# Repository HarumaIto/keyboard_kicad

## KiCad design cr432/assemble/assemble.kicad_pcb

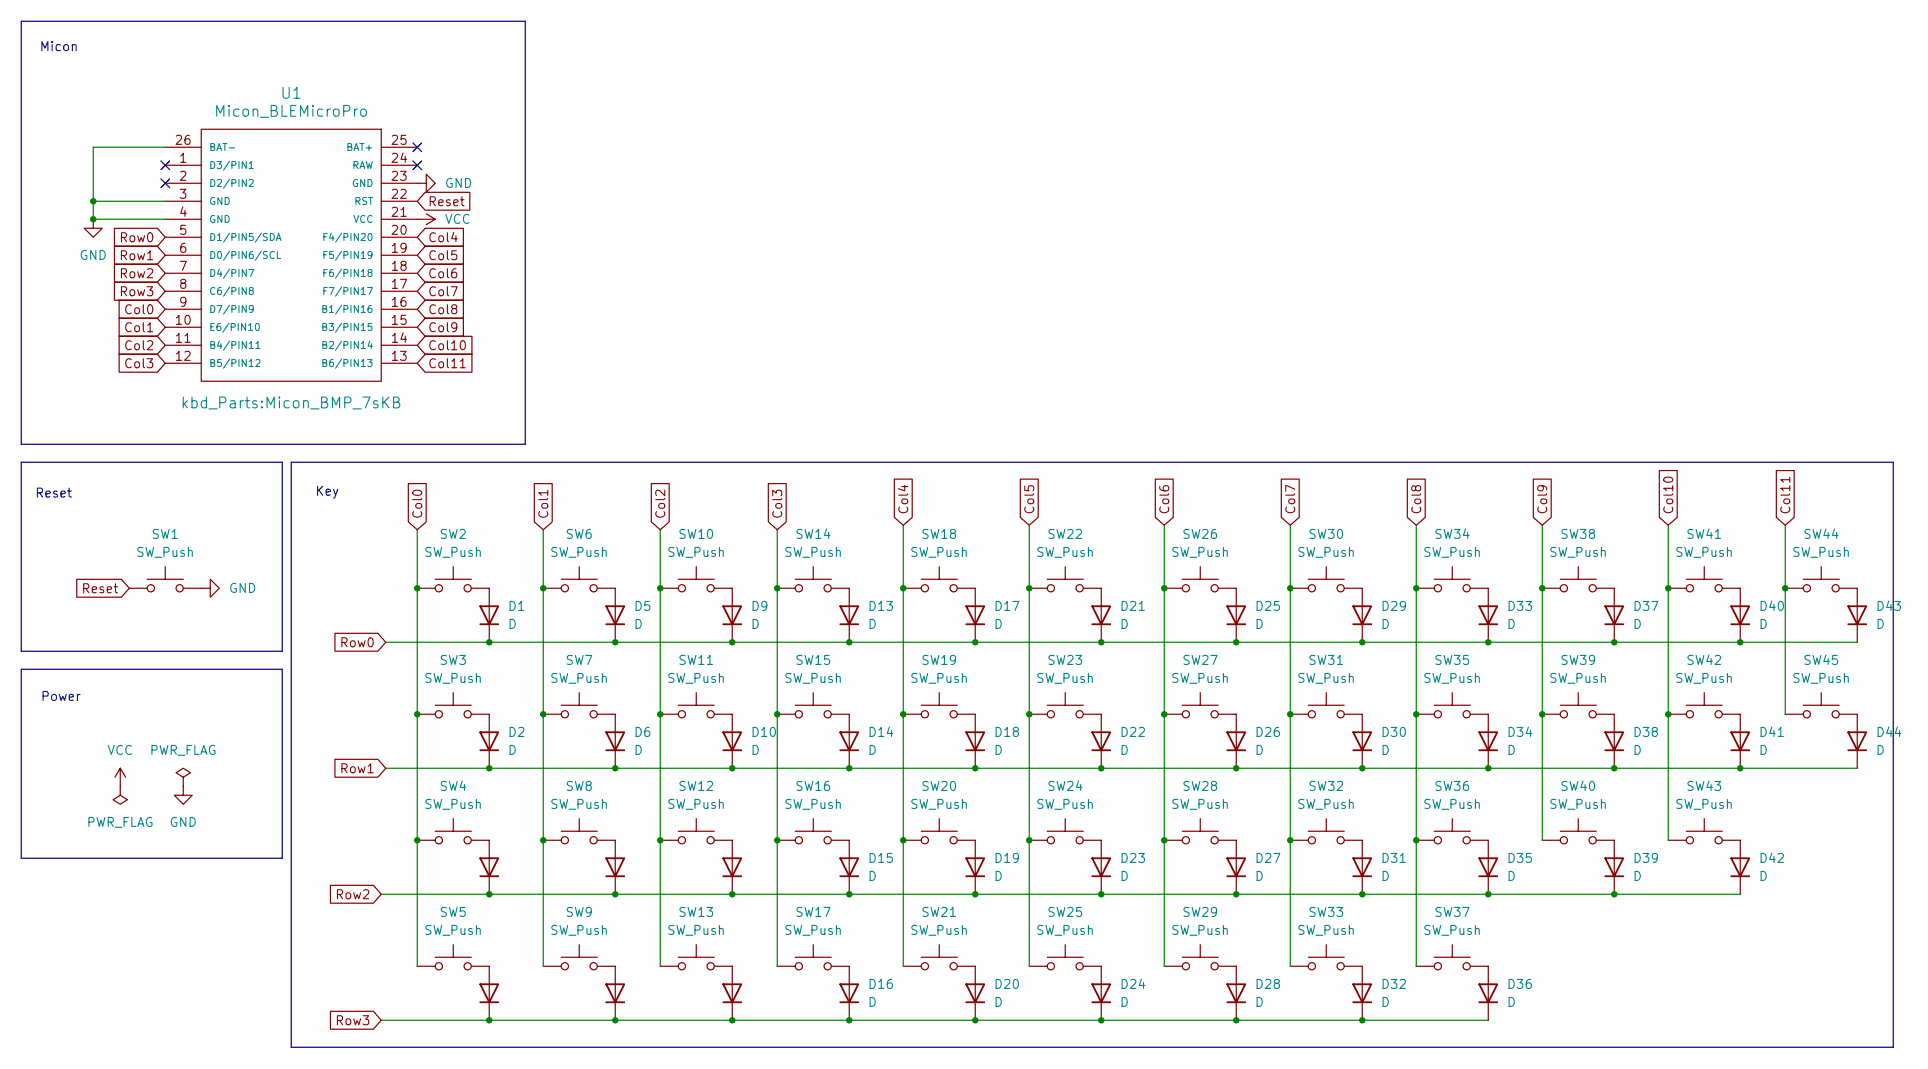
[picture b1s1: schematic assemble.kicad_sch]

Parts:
D1, D2, D3, D4, D5, D6, D7, D8, D9, D10, D11, D12, D13, D14, D15, D16, D17, D18, D19, D20, D21, D22, D23, D24, D25, D26, D27, D28, D29, D30, D31, D32, D33, D34, D35, D36, D37, D38, D39, D40, D41, D42, D43, D44: D; Diode_SMD
SW1: SW_Push; ResetSW
SW2, SW6, SW7, SW8, SW10, SW11, SW12, SW14, SW15, SW16, SW18, SW19, SW20, SW21, SW22, SW23, SW24, SW26, SW27, SW28, SW30, SW31, SW32, SW34, SW35, SW36, SW38, SW39, SW40, SW41, SW42: SW_Push; CherryMX_Hotswap_1u
SW3, SW5, SW9, SW13, SW29, SW33, SW37, SW45: SW_Push; CherryMX_Hotswap_1.25u
SW4, SW43: SW_Push; CherryMX_Hotswap_1.75u
SW17, SW25: SW_Push; CherryMX_Hotswap_2u
SW44: SW_Push; CherryMX_Hotswap_1.5u
U1: Micon_BLEMicroPro; Micon_BMP_7sKB

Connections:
Col0: SW2.1, SW3.1, SW4.1, SW5.1, U1.9 (D7/PIN9)
Col1: SW6.1, SW7.1, SW8.1, SW9.1, U1.10 (E6/PIN10)
Col2: SW10.1, SW11.1, SW12.1, SW13.1, U1.11 (B4/PIN11)
Col3: SW14.1, SW15.1, SW16.1, SW17.1, U1.12 (B5/PIN12)
Col4: SW18.1, SW19.1, SW20.1, SW21.1, U1.20 (F4/PIN20)
Col5: SW22.1, SW23.1, SW24.1, SW25.1, U1.19 (F5/PIN19)
Col6: SW26.1, SW27.1, SW28.1, SW29.1, U1.18 (F6/PIN18)
Col7: SW30.1, SW31.1, SW32.1, SW33.1, U1.17 (F7/PIN17)
Col8: SW34.1, SW35.1, SW36.1, SW37.1, U1.16 (B1/PIN16)
Col9: SW38.1, SW39.1, SW40.1, U1.15 (B3/PIN15)
Col10: SW41.1, SW42.1, SW43.1, U1.14 (B2/PIN14)
Col11: SW44.1, SW45.1, U1.13 (B6/PIN13)
GND: SW1.2, U1.3 (GND), U1.4 (GND), U1.23 (GND), U1.26 (BAT-)
unnamed: D1.2 (A), SW2.2
unnamed: D2.2 (A), SW3.2
unnamed: D3.2 (A), SW4.2
unnamed: D4.2 (A), SW5.2
unnamed: D5.2 (A), SW6.2
unnamed: D6.2 (A), SW7.2
unnamed: D7.2 (A), SW8.2
unnamed: D8.2 (A), SW9.2
unnamed: D9.2 (A), SW10.2
unnamed: D10.2 (A), SW11.2
unnamed: D11.2 (A), SW12.2
unnamed: D12.2 (A), SW13.2
unnamed: D13.2 (A), SW14.2
unnamed: D14.2 (A), SW15.2
unnamed: D15.2 (A), SW16.2
unnamed: D16.2 (A), SW17.2
unnamed: D17.2 (A), SW18.2
unnamed: D18.2 (A), SW19.2
unnamed: D19.2 (A), SW20.2
unnamed: D20.2 (A), SW21.2
unnamed: D21.2 (A), SW22.2
unnamed: D22.2 (A), SW23.2
unnamed: D23.2 (A), SW24.2
unnamed: D24.2 (A), SW25.2
unnamed: D25.2 (A), SW26.2
unnamed: D26.2 (A), SW27.2
unnamed: D27.2 (A), SW28.2
unnamed: D28.2 (A), SW29.2
unnamed: D29.2 (A), SW30.2
unnamed: D30.2 (A), SW31.2
unnamed: D31.2 (A), SW32.2
unnamed: D32.2 (A), SW33.2
unnamed: D33.2 (A), SW34.2
unnamed: D34.2 (A), SW35.2
unnamed: D35.2 (A), SW36.2
unnamed: D36.2 (A), SW37.2
unnamed: D37.2 (A), SW38.2
unnamed: D38.2 (A), SW39.2
unnamed: D39.2 (A), SW40.2
unnamed: D40.2 (A), SW41.2
unnamed: D41.2 (A), SW42.2
unnamed: D42.2 (A), SW43.2
unnamed: D43.2 (A), SW44.2
unnamed: D44.2 (A), SW45.2
Reset: SW1.1, U1.22 (RST)
Row0: D1.1 (K), D5.1 (K), D9.1 (K), D13.1 (K), D17.1 (K), D21.1 (K), D25.1 (K), D29.1 (K), D33.1 (K), D37.1 (K), D40.1 (K), D43.1 (K), U1.5 (D1/PIN5/SDA)
Row1: D2.1 (K), D6.1 (K), D10.1 (K), D14.1 (K), D18.1 (K), D22.1 (K), D26.1 (K), D30.1 (K), D34.1 (K), D38.1 (K), D41.1 (K), D44.1 (K), U1.6 (D0/PIN6/SCL)
Row2: D3.1 (K), D7.1 (K), D11.1 (K), D15.1 (K), D19.1 (K), D23.1 (K), D27.1 (K), D31.1 (K), D35.1 (K), D39.1 (K), D42.1 (K), U1.7 (D4/PIN7)
Row3: D4.1 (K), D8.1 (K), D12.1 (K), D16.1 (K), D20.1 (K), D24.1 (K), D28.1 (K), D32.1 (K), D36.1 (K), U1.8 (C6/PIN8)
VCC: U1.21 (VCC)

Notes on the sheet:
Power
Micon
Reset
Key

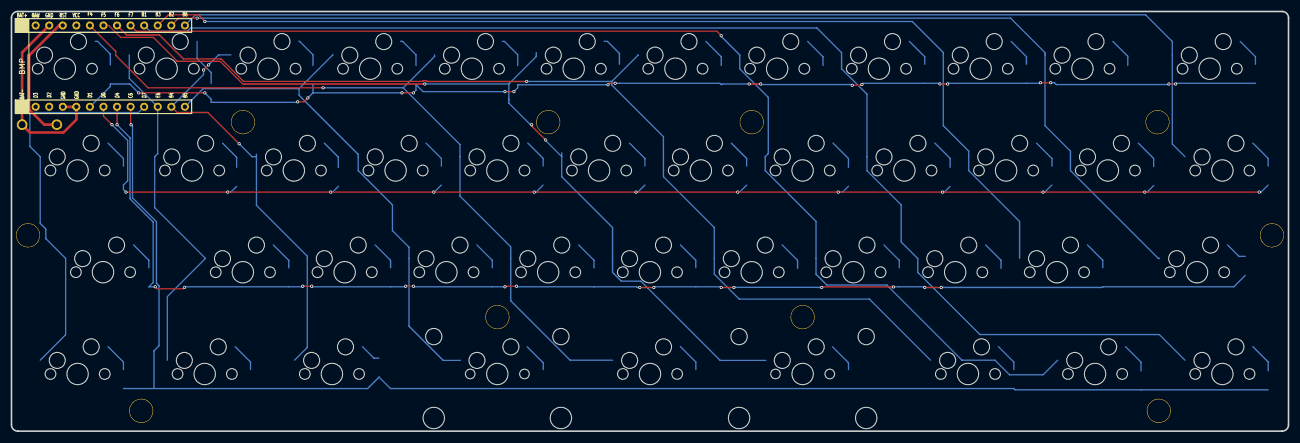
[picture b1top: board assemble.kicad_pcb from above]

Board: 2 copper layers, 239.1 x 78.6 mm, 100 parts (0 on the bottom side), 62 nets.

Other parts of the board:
Ref**: Val**; m2_Spacer_Hole
Ref**#2, Ref**#3, Ref**#4, Ref**#5, Ref**#6, Ref**#7, Ref**#8, Ref**#9, Ref**#10: Val**; m2_Spacer_Hole

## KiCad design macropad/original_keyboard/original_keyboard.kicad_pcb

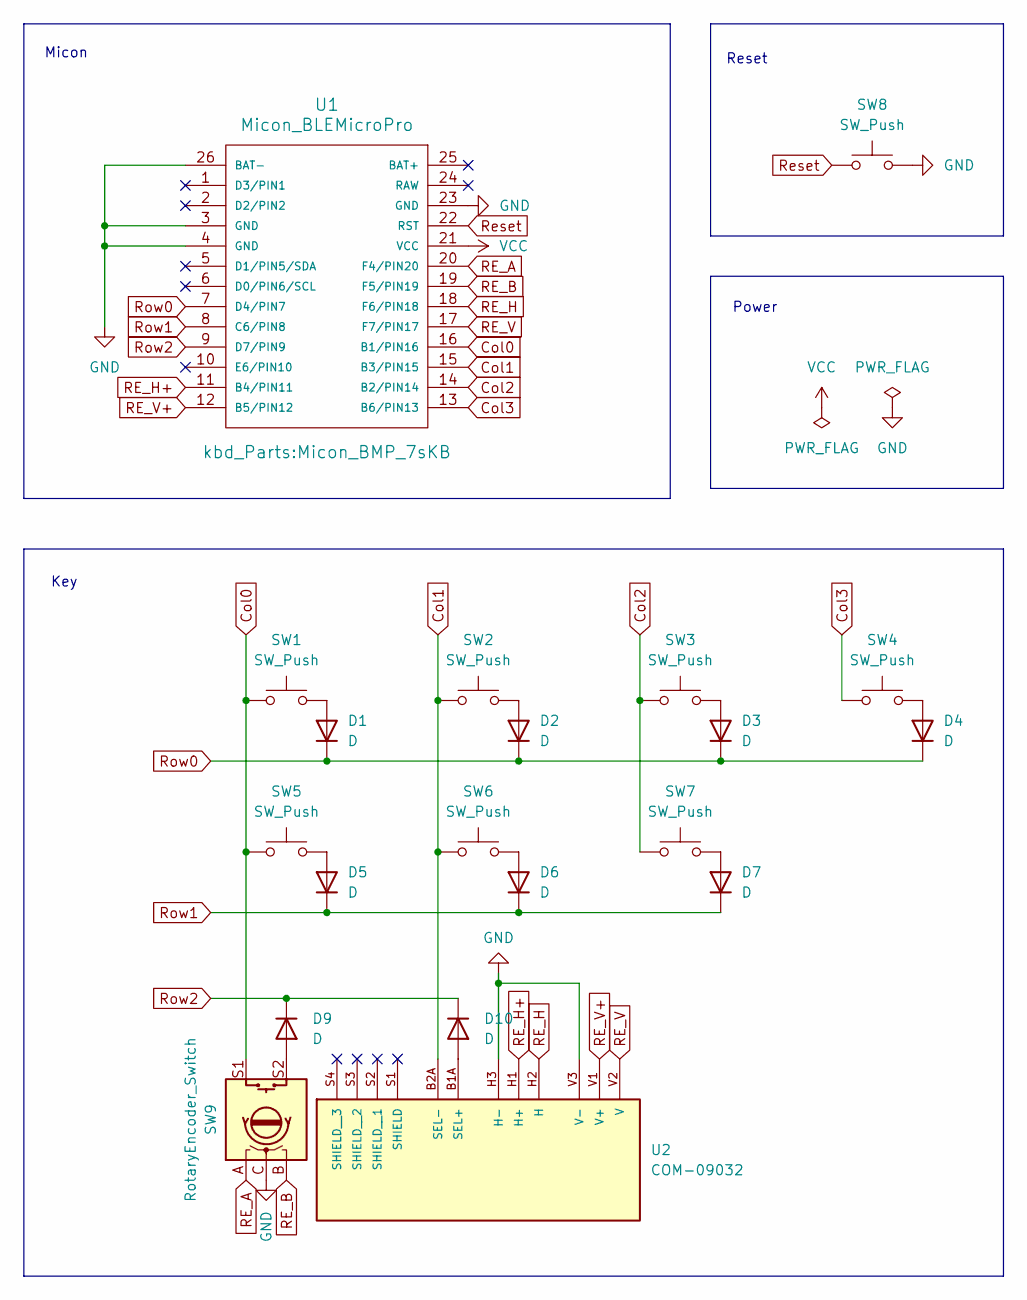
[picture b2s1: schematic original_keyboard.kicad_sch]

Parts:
D1, D2, D3, D4, D5, D6, D7, D9, D10: D; Diode_TH_SMD
SW1, SW2, SW3, SW4, SW5, SW6, SW7: SW_Push; Choc_v1_v2
SW8: SW_Push; ResetSW
SW9: RotaryEncoder_Switch; EVQWGD001
U1: Micon_BLEMicroPro; Micon_BMP_7sKB
U2: COM-09032; XDCR_COM-09032; PARTREV N/A

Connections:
Col0: SW1.1, SW5.1, SW9.S1, U1.16 (B1/PIN16)
Col1: SW2.1, SW6.1, U1.15 (B3/PIN15), U2.B2A (SEL-)
Col2: SW3.1, SW7.1, U1.14 (B2/PIN14)
Col3: SW4.1, U1.13 (B6/PIN13)
GND: SW8.2, SW9.C, U1.3 (GND), U1.4 (GND), U1.23 (GND), U1.26 (BAT-), U2.H3 (H-), U2.V3 (V-)
unnamed: D1.2 (A), SW1.2
unnamed: D2.2 (A), SW2.2
unnamed: D3.2 (A), SW3.2
unnamed: D4.2 (A), SW4.2
unnamed: D5.2 (A), SW5.2
unnamed: D6.2 (A), SW6.2
unnamed: D7.2 (A), SW7.2
unnamed: D9.2 (A), SW9.S2
unnamed: D10.2 (A), U2.B1A (SEL+)
RE_A: SW9.A, U1.20 (F4/PIN20)
RE_B: SW9.B, U1.19 (F5/PIN19)
RE_H: U1.18 (F6/PIN18), U2.H2 (H)
RE_H+: U1.11 (B4/PIN11), U2.H1 (H+)
RE_V: U1.17 (F7/PIN17), U2.V2 (V)
RE_V+: U1.12 (B5/PIN12), U2.V1 (V+)
Reset: SW8.1, U1.22 (RST)
Row0: D1.1 (K), D2.1 (K), D3.1 (K), D4.1 (K), U1.7 (D4/PIN7)
Row1: D5.1 (K), D6.1 (K), D7.1 (K), U1.8 (C6/PIN8)
Row2: D9.1 (K), D10.1 (K), U1.9 (D7/PIN9)
VCC: U1.21 (VCC)

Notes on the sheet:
Reset
Power
Micon
Key

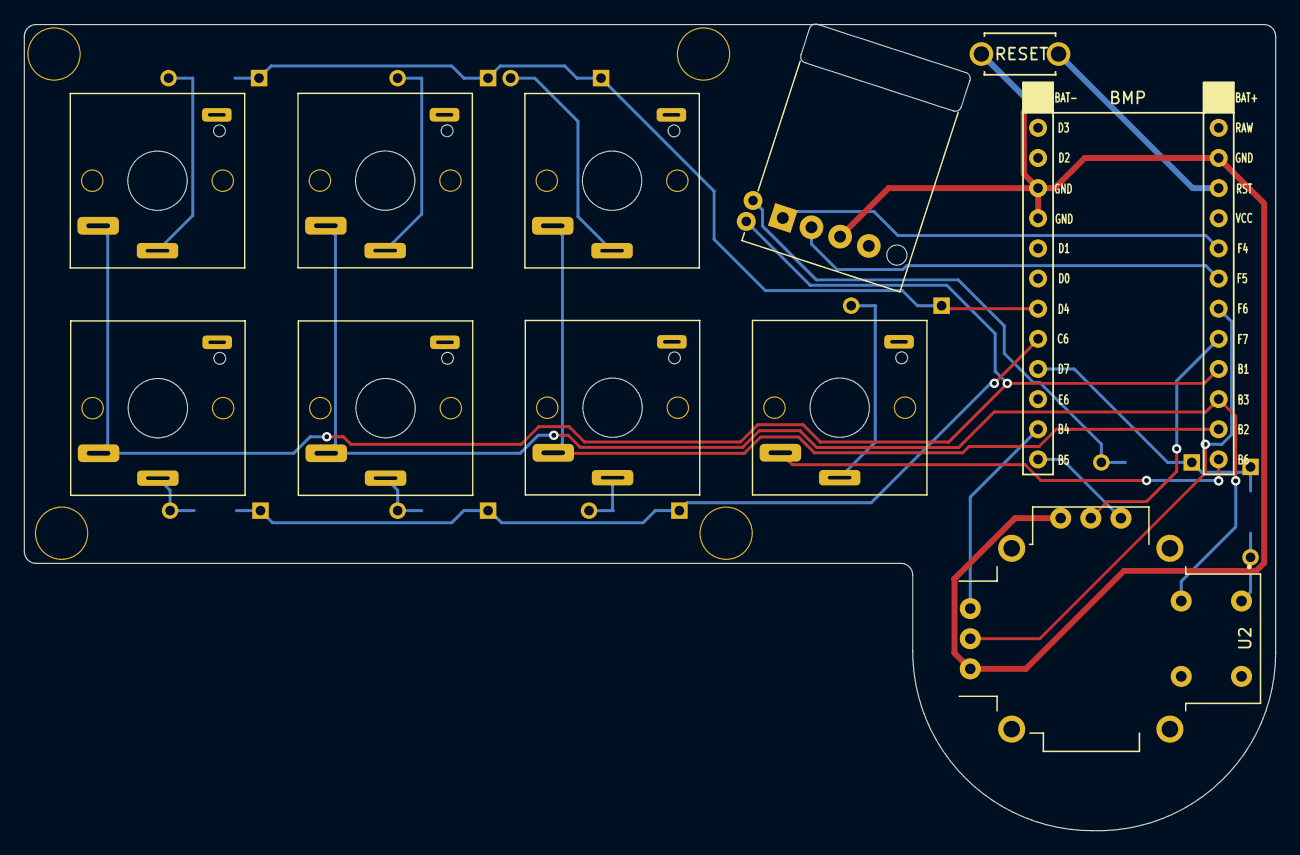
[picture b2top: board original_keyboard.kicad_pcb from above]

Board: 2 copper layers, 105.5 x 68.0 mm, 24 parts (1 on the bottom side), 24 nets.

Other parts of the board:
Ref**: Val**; m2_Spacer_Hole
Ref**#2, Ref**#3, Ref**#4: Val**; m2_Spacer_Hole

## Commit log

2025-03-09 rev1
